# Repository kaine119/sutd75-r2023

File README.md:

# sutd-board-r2023
sutd kebord (manu + workshop early 2023)

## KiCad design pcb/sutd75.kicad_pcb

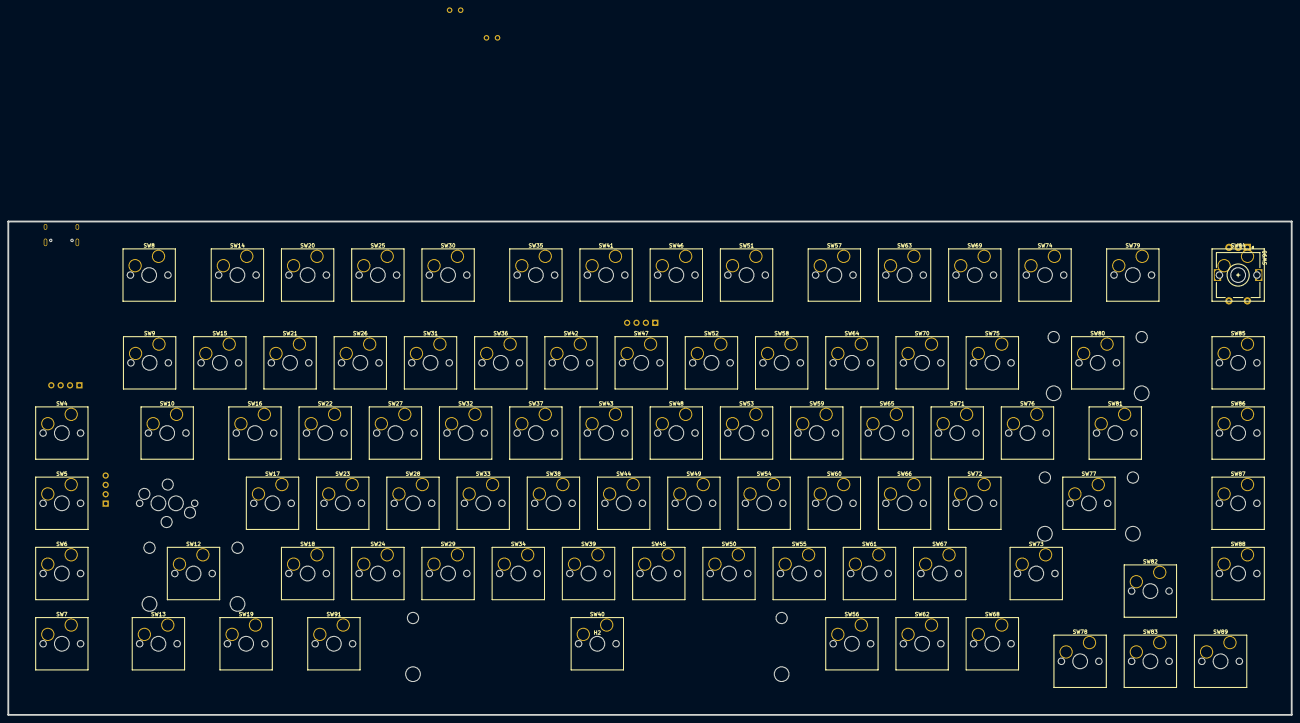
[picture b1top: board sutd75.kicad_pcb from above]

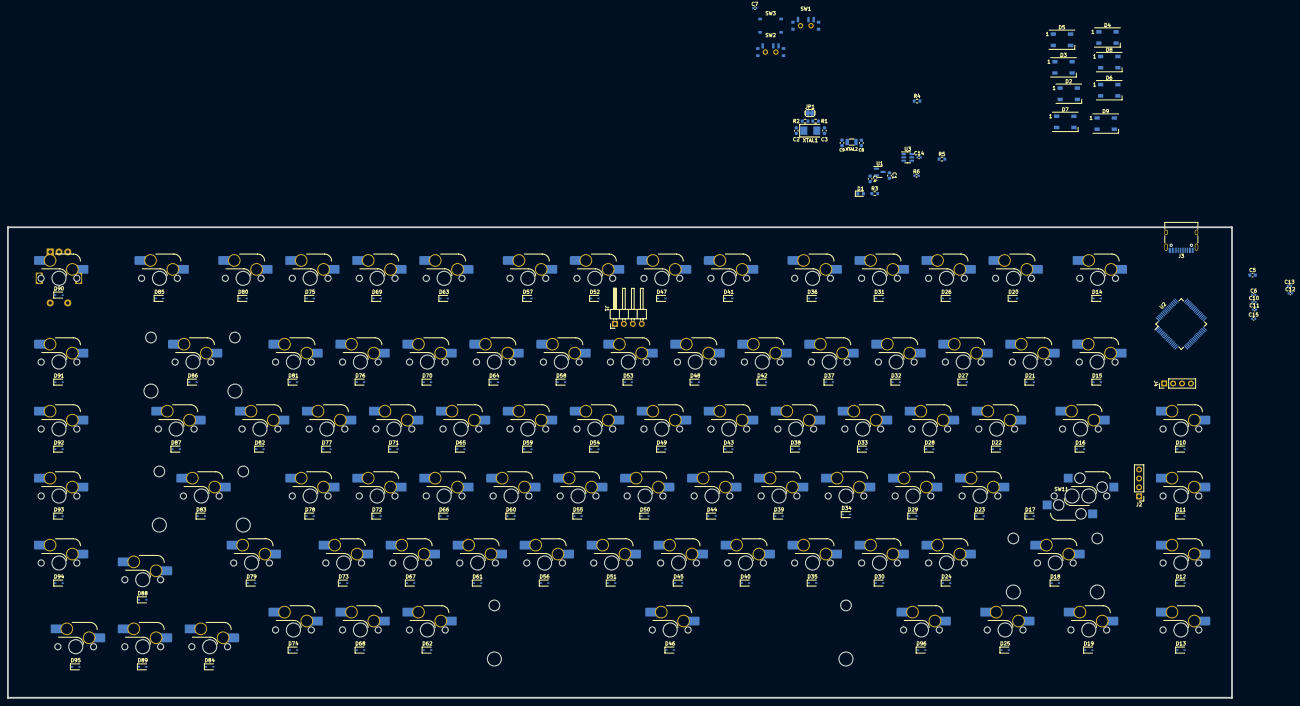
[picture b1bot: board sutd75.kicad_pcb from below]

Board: 2 copper layers, 348.1 x 133.8 mm, 222 parts (131 on the bottom side), 141 nets, no tracks yet.

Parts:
C1, C4: 1uF; C_0603_1608Metric
C2, C3: 30pF; C_0603_1608Metric
C5: 10uF; C_0603_1608Metric
C6, C7, C10, C11, C12, C13, C14, C15: 100nF; C_0402_1005Metric
C8, C9: 15pF; C_0603_1608Metric
D1: BLUE; LED_0603_1608Metric
D2, D3, D4, D5, D6, D7, D8, D9: WS2812B; LED_WS2812B_PLCC4_5.0x5.0mm_P3.2mm
D10, D11, D12, D13, D14, D15, D16, D17, D18, D19, D20, D21, D22, D23, D24, D25, D26, D27, D28, D29, D30, D31, D32, D33, D34, D35, D36, D37, D38, D39, D40, D41, D42, D43, D44, D45, D46, D47, D48, D49, D50, D51, D52, D53, D54, D55, D56, D57, D58, D59, D60, D61, D62, D63, D64, D65, D66, D67, D68, D69, D70, D71, D72, D73, D74, D75, D76, D77, D78, D79, D80, D81, D82, D83, D84, D85, D86, D87, D88, D89, D90, D91, D92, D93, D94, D95, D96: D; D_SOD-323
H1: LShift; Stabilizer_Cherry_MX_2u
H2: Space; Stabilizer_Cherry_MX_6.25u
H3: Enter; Stabilizer_Cherry_MX_2u
H4: Backspace; Stabilizer_Cherry_MX_2u
J1: SWD Header; PinHeader_1x04_P2.54mm_Horizontal
J2: UART header; PinHeader_1x04_P2.54mm_Vertical
J3: USB_C_Receptacle_USB2.0; USB_C_Receptacle_HRO_TYPE-C-31-M-12
J4: I2C header; PinHeader_1x04_P2.54mm_Vertical
JP1: SolderJumper_2_Open; SolderJumper-2_P1.3mm_Open_RoundedPad1.0x1.5mm
R1, R2: 200; R_0603_1608Metric
R3: 100; R_0603_1608Metric
R4, R5: 5.1k; R_0603_1608Metric
R6: 1.5k; R_0402_1005Metric_Pad0.72x0.64mm_HandSolder
SW1: BOOT0; SW_SPDTx01_SMD_AlpsAlpine-SSSS811101
SW2: BOOT1; SW_SPDTx01_SMD_AlpsAlpine-SSSS811101
SW3: RESET; SW_Push_SMD-SW-4_5.1x5.1x1.5
SW4: M1; SW_Hotswap_Kailh_MX_plated_1.00u
SW5: M2; SW_Hotswap_Kailh_MX_plated_1.00u
SW6: M3; SW_Hotswap_Kailh_MX_plated_1.00u
SW7: M4; SW_Hotswap_Kailh_MX_plated_1.00u
SW8: Esc; SW_Hotswap_Kailh_MX_plated_1.00u
SW9: Tilde; SW_Hotswap_Kailh_MX_plated_1.00u
SW10: Tab; SW_Hotswap_Kailh_MX_plated_1.50u
SW11: CapsLock; SW_Hotswap_Kailh_MX_1.75u_SteppedCapsLock
SW12: Shift; SW_Hotswap_Kailh_MX_plated_2.25u
SW13: Ctrl; SW_Hotswap_Kailh_MX_plated_1.25u
SW14: F1; SW_Hotswap_Kailh_MX_plated_1.00u
SW15: 1; SW_Hotswap_Kailh_MX_plated_1.00u
SW16: Q; SW_Hotswap_Kailh_MX_plated_1.00u
SW17: A; SW_Hotswap_Kailh_MX_plated_1.00u
SW18: Z; SW_Hotswap_Kailh_MX_plated_1.00u
SW19: Win; SW_Hotswap_Kailh_MX_plated_1.25u
SW20: F2; SW_Hotswap_Kailh_MX_plated_1.00u
SW21: 2; SW_Hotswap_Kailh_MX_plated_1.00u
SW22: W; SW_Hotswap_Kailh_MX_plated_1.00u
SW23: S; SW_Hotswap_Kailh_MX_plated_1.00u
SW24: X; SW_Hotswap_Kailh_MX_plated_1.00u
SW25: F3; SW_Hotswap_Kailh_MX_plated_1.00u
SW26: 3; SW_Hotswap_Kailh_MX_plated_1.00u
SW27: E; SW_Hotswap_Kailh_MX_plated_1.00u
SW28: D; SW_Hotswap_Kailh_MX_plated_1.00u
SW29: C; SW_Hotswap_Kailh_MX_plated_1.00u
SW30: F4; SW_Hotswap_Kailh_MX_plated_1.00u
SW31: 4; SW_Hotswap_Kailh_MX_plated_1.00u
SW32: R; SW_Hotswap_Kailh_MX_plated_1.00u
SW33: F; SW_Hotswap_Kailh_MX_plated_1.00u
SW34: V; SW_Hotswap_Kailh_MX_plated_1.00u
SW35: F5; SW_Hotswap_Kailh_MX_plated_1.00u
SW36: 5; SW_Hotswap_Kailh_MX_plated_1.00u
SW37: T; SW_Hotswap_Kailh_MX_plated_1.00u
SW38: G; SW_Hotswap_Kailh_MX_plated_1.00u
SW39: B; SW_Hotswap_Kailh_MX_plated_1.00u
SW40: Space; SW_Hotswap_Kailh_MX_plated_6.25u
SW41: F6; SW_Hotswap_Kailh_MX_plated_1.00u
SW42: 6; SW_Hotswap_Kailh_MX_plated_1.00u
SW43: Y; SW_Hotswap_Kailh_MX_plated_1.00u
SW44: H; SW_Hotswap_Kailh_MX_plated_1.00u
SW45: N; SW_Hotswap_Kailh_MX_plated_1.00u
SW46: F7; SW_Hotswap_Kailh_MX_plated_1.00u
SW47: 7; SW_Hotswap_Kailh_MX_plated_1.00u
SW48: U; SW_Hotswap_Kailh_MX_plated_1.00u
SW49: J; SW_Hotswap_Kailh_MX_plated_1.00u
SW50: M; SW_Hotswap_Kailh_MX_plated_1.00u
SW51: F8; SW_Hotswap_Kailh_MX_plated_1.00u
SW52: 8; SW_Hotswap_Kailh_MX_plated_1.00u
SW53: I; SW_Hotswap_Kailh_MX_plated_1.00u
SW54: K; SW_Hotswap_Kailh_MX_plated_1.00u
SW55: Comma; SW_Hotswap_Kailh_MX_plated_1.00u
SW56: RAlt; SW_Hotswap_Kailh_MX_plated_1.00u
SW57: F9; SW_Hotswap_Kailh_MX_plated_1.00u
SW58: 9; SW_Hotswap_Kailh_MX_plated_1.00u
SW59: O; SW_Hotswap_Kailh_MX_plated_1.00u
SW60: L; SW_Hotswap_Kailh_MX_plated_1.00u
SW61: Period; SW_Hotswap_Kailh_MX_plated_1.00u
SW62: RFn; SW_Hotswap_Kailh_MX_plated_1.00u
SW63: F10; SW_Hotswap_Kailh_MX_plated_1.00u
SW64: 0; SW_Hotswap_Kailh_MX_plated_1.00u
SW65: P; SW_Hotswap_Kailh_MX_plated_1.00u
SW66: Semicolon; SW_Hotswap_Kailh_MX_plated_1.00u
SW67: Slash; SW_Hotswap_Kailh_MX_plated_1.00u
SW68: RCtrl; SW_Hotswap_Kailh_MX_plated_1.00u
SW69: F11; SW_Hotswap_Kailh_MX_plated_1.00u
SW70: Minus; SW_Hotswap_Kailh_MX_plated_1.00u
SW71: LBrkt; SW_Hotswap_Kailh_MX_plated_1.00u
SW72: Quote; SW_Hotswap_Kailh_MX_plated_1.00u
SW73: RShift; SW_Hotswap_Kailh_MX_plated_1.75u
SW74: F12; SW_Hotswap_Kailh_MX_plated_1.00u
SW75: Equals; SW_Hotswap_Kailh_MX_plated_1.00u
SW76: RBrkt; SW_Hotswap_Kailh_MX_plated_1.00u
SW77: Enter; SW_Hotswap_Kailh_MX_plated_2.25u
SW78: LArr; SW_Hotswap_Kailh_MX_plated_1.00u
SW79: F13; SW_Hotswap_Kailh_MX_plated_1.00u
SW80: Bksp; SW_Hotswap_Kailh_MX_plated_2.00u
SW81: Bkslash; SW_Hotswap_Kailh_MX_plated_1.50u
SW82: UArr; SW_Hotswap_Kailh_MX_plated_1.00u
SW83: DArr; SW_Hotswap_Kailh_MX_plated_1.00u
SW84: Knob; SW_Hotswap_Kailh_MX_plated_1.00u
SW85: Home; SW_Hotswap_Kailh_MX_plated_1.00u
SW86: PgUp; SW_Hotswap_Kailh_MX_plated_1.00u
SW87: PgDn; SW_Hotswap_Kailh_MX_plated_1.00u
SW88: End; SW_Hotswap_Kailh_MX_plated_1.00u
SW89: RArr; SW_Hotswap_Kailh_MX_plated_1.00u
SW90: Rotary_Encoder_Switch; RotaryEncoder_Alps_EC11E-Switch_Vertical_H20mm
SW91: Alt; SW_Hotswap_Kailh_MX_plated_1.25u
U1: XC6206PxxxMR; SOT-23
U2: STM32F103RBTx; LQFP-64_10x10mm_P0.5mm
U3: USBLC6-2SC6; SOT-23-6
XTAL1: 8MHz; Crystal_SMD_5032-2Pin_5.0x3.2mm
XTAL2: 32.768kHz; Crystal_SMD_3215-2Pin_3.2x1.5mm

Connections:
+3V3: C4.1, C5.1, C6.1, C10.1, C11.1, C12.1, C13.2, C15.1, D1.2 (A), J1.4, J4.2, R6.1, SW1.1 (A), SW2.1 (A), U1.2 (VO), U2.1 (VBAT), U2.13 (VDDA), U2.19 (VDD), U2.32 (VDD), U2.48 (VDD), U2.64 (VDD)
/BOOT0: SW1.2 (B), U2.60 (BOOT0)
/BOOT1: SW2.2 (B), U2.28 (PB2)
/COL1: SW4.1, SW5.1, SW6.1, SW7.1, U2.35 (PB14)
/COL2: SW8.1, SW9.1, SW10.1, SW11.1, SW12.1, SW13.1, U2.34 (PB13)
/COL3: SW14.1, SW15.1, SW16.1, SW17.1, SW18.1, SW19.1, U2.33 (PB12)
/COL4: SW20.1, SW21.1, SW22.1, SW23.1, SW24.1, SW91.1, U2.30 (PB11)
/COL5: SW25.1, SW26.1, SW27.1, SW28.1, SW29.1, U2.29 (PB10)
/COL6: SW30.1, SW31.1, SW32.1, SW33.1, SW34.1, U2.27 (PB1)
/COL7: SW35.1, SW36.1, SW37.1, SW38.1, SW39.1, SW40.1, U2.26 (PB0)
/COL8: SW41.1, SW42.1, SW43.1, SW44.1, SW45.1, U2.36 (PB15)
/COL9: SW46.1, SW47.1, SW48.1, SW49.1, SW50.1, U2.62 (PB9)
/COL10: SW51.1, SW52.1, SW53.1, SW54.1, SW55.1, SW56.1, U2.61 (PB8)
/COL11: SW57.1, SW58.1, SW59.1, SW60.1, SW61.1, SW62.1, U2.59 (PB7)
/COL12: SW63.1, SW64.1, SW65.1, SW66.1, SW67.1, SW68.1, U2.58 (PB6)
/COL13: SW69.1, SW70.1, SW71.1, SW72.1, SW73.1, U2.57 (PB5)
/COL14: SW74.1, SW75.1, SW76.1, SW77.1, SW78.1, U2.56 (PB4)
/COL15: SW79.1, SW80.1, SW81.1, SW82.1, SW83.1, U2.55 (PB3)
/COL16: SW84.1, SW85.1, SW86.1, SW87.1, SW88.1, SW89.1, SW90.S1, U2.50 (PA15)
/HSE_IN: C2.1, U2.5 (PD0), XTAL1.1
/HSE_OUT: JP1.2 (B), R2.2, U2.6 (PD1)
/KNOB_A: SW90.A, U2.23 (PA7)
/KNOB_B: SW90.B, U2.22 (PA6)
/LSE_IN: C8.1, U2.3 (PC14), XTAL2.1
/LSE_OUT: C9.2, U2.4 (PC15), XTAL2.2
/NRST: C7.2, SW3.1, U2.7 (NRST)
/ROW1: D14.2 (A), D20.2 (A), D26.2 (A), D31.2 (A), D36.2 (A), D41.2 (A), D47.2 (A), D52.2 (A), D57.2 (A), D63.2 (A), D69.2 (A), D75.2 (A), D80.2 (A), D85.2 (A), D90.2 (A), U2.14 (PA0)
/ROW2: D15.2 (A), D21.2 (A), D27.2 (A), D32.2 (A), D37.2 (A), D42.2 (A), D48.2 (A), D53.2 (A), D58.2 (A), D64.2 (A), D70.2 (A), D76.2 (A), D81.2 (A), D86.2 (A), D91.2 (A), U2.15 (PA1)
/ROW3: D10.2 (A), D16.2 (A), D22.2 (A), D28.2 (A), D33.2 (A), D38.2 (A), D43.2 (A), D49.2 (A), D54.2 (A), D59.2 (A), D65.2 (A), D71.2 (A), D77.2 (A), D82.2 (A), D87.2 (A), D92.2 (A), U2.16 (PA2)
/ROW4: D11.2 (A), D17.2 (A), D23.2 (A), D29.2 (A), D34.2 (A), D39.2 (A), D44.2 (A), D50.2 (A), D55.2 (A), D60.2 (A), D66.2 (A), D72.2 (A), D78.2 (A), D83.2 (A), D93.2 (A), U2.17 (PA3)
/ROW5: D12.2 (A), D18.2 (A), D24.2 (A), D30.2 (A), D35.2 (A), D40.2 (A), D45.2 (A), D51.2 (A), D56.2 (A), D61.2 (A), D67.2 (A), D73.2 (A), D79.2 (A), D88.2 (A), D94.2 (A), U2.20 (PA4)
/ROW6: D13.2 (A), D19.2 (A), D25.2 (A), D46.2 (A), D62.2 (A), D68.2 (A), D74.2 (A), D84.2 (A), D89.2 (A), D95.2 (A), D96.2 (A), U2.21 (PA5)
/SWCLK: J1.2, U2.49 (PA14)
/SWDIO: J1.3, U2.46 (PA13)
/UART1_RX: J2.2, U2.43 (PA10)
/UART1_TX: J2.3, U2.42 (PA9)
/USB_CC1: J3.B5 (CC2), R5.1
/USB_CC2: J3.A5 (CC1), R4.1
/USB_D+: R6.2, U2.45 (PA12), U3.4 (I/O2)
/USB_D-: U2.44 (PA11), U3.6 (I/O1)
GND: C1.2, C2.2, C3.2, C4.2, C5.2, C6.2, C7.1, C8.2, C9.1, C10.2, C11.2, C12.2, C13.1, C14.2, C15.2, D2.1 (VDD), D3.1 (VDD), D4.1 (VDD), D5.1 (VDD), D6.3 (VSS), D7.3 (VSS), D8.3 (VSS), D9.3 (VSS), J1.1, J2.4, J3.A1 (GND), J3.A12 (GND), J3.B1 (GND), J3.B12 (GND), J3.S1 (SHIELD), J4.1, R3.1, R4.2, R5.2, SW1.3 (C), SW2.3 (C), SW3.2, SW90.C, U1.1 (GND), U2.12 (VSSA), U2.18 (VSS), U2.31 (VSS), U2.47 (VSS), U2.63 (VSS), U3.2 (GND)
unnamed: C3.1, JP1.1 (A), R1.1, XTAL1.2
unnamed: D1.1 (K), R3.2
unnamed: D2.2 (DOUT), D3.4 (DIN)
unnamed: D3.2 (DOUT), D4.4 (DIN)
unnamed: D4.2 (DOUT), D5.4 (DIN)
unnamed: D5.2 (DOUT), D9.4 (DIN)
unnamed: D6.4 (DIN), D7.2 (DOUT)
unnamed: D7.4 (DIN), D8.2 (DOUT)
unnamed: D8.4 (DIN), D9.2 (DOUT)
unnamed: D10.1 (K), SW4.2
unnamed: D11.1 (K), SW5.2
unnamed: D12.1 (K), SW6.2
unnamed: D13.1 (K), SW7.2
unnamed: D14.1 (K), SW8.2
unnamed: D15.1 (K), SW9.2
unnamed: D16.1 (K), SW10.2
unnamed: D17.1 (K), SW11.2
unnamed: D18.1 (K), SW12.2
unnamed: D19.1 (K), SW13.2
unnamed: D20.1 (K), SW14.2
unnamed: D21.1 (K), SW15.2
unnamed: D22.1 (K), SW16.2
unnamed: D23.1 (K), SW17.2
unnamed: D24.1 (K), SW18.2
unnamed: D25.1 (K), SW19.2
unnamed: D26.1 (K), SW20.2
unnamed: D27.1 (K), SW21.2
unnamed: D28.1 (K), SW22.2
unnamed: D29.1 (K), SW23.2
unnamed: D30.1 (K), SW24.2
unnamed: D31.1 (K), SW25.2
unnamed: D32.1 (K), SW26.2
unnamed: D33.1 (K), SW27.2
unnamed: D34.1 (K), SW28.2
unnamed: D35.1 (K), SW29.2
unnamed: D36.1 (K), SW30.2
unnamed: D37.1 (K), SW31.2
unnamed: D38.1 (K), SW32.2
unnamed: D39.1 (K), SW33.2
unnamed: D40.1 (K), SW34.2
unnamed: D41.1 (K), SW35.2
unnamed: D42.1 (K), SW36.2
unnamed: D43.1 (K), SW37.2
unnamed: D44.1 (K), SW38.2
unnamed: D45.1 (K), SW39.2
unnamed: D46.1 (K), SW40.2
unnamed: D47.1 (K), SW41.2
unnamed: D48.1 (K), SW42.2
unnamed: D49.1 (K), SW43.2
unnamed: D50.1 (K), SW44.2
unnamed: D51.1 (K), SW45.2
unnamed: D52.1 (K), SW46.2
unnamed: D53.1 (K), SW47.2
unnamed: D54.1 (K), SW48.2
unnamed: D55.1 (K), SW49.2
unnamed: D56.1 (K), SW50.2
unnamed: D57.1 (K), SW51.2
unnamed: D58.1 (K), SW52.2
unnamed: D59.1 (K), SW53.2
unnamed: D60.1 (K), SW54.2
unnamed: D61.1 (K), SW55.2
unnamed: D62.1 (K), SW56.2
unnamed: D63.1 (K), SW57.2
unnamed: D64.1 (K), SW58.2
unnamed: D65.1 (K), SW59.2
unnamed: D66.1 (K), SW60.2
unnamed: D67.1 (K), SW61.2
unnamed: D68.1 (K), SW62.2
unnamed: D69.1 (K), SW63.2
unnamed: D70.1 (K), SW64.2
unnamed: D71.1 (K), SW65.2
unnamed: D72.1 (K), SW66.2
unnamed: D73.1 (K), SW67.2
unnamed: D74.1 (K), SW68.2
unnamed: D75.1 (K), SW69.2
unnamed: D76.1 (K), SW70.2
unnamed: D77.1 (K), SW71.2
unnamed: D78.1 (K), SW72.2
unnamed: D79.1 (K), SW73.2
unnamed: D80.1 (K), SW74.2
unnamed: D82.1 (K), SW76.2
unnamed: D83.1 (K), SW77.2
unnamed: D84.1 (K), SW78.2
unnamed: D85.1 (K), SW79.2
unnamed: D86.1 (K), SW80.2
unnamed: D87.1 (K), SW81.2
unnamed: D88.1 (K), SW82.2
unnamed: D89.1 (K), SW83.2
unnamed: D90.1 (K), SW84.2, SW90.S2
unnamed: D91.1 (K), SW85.2
unnamed: D92.1 (K), SW86.2
unnamed: D93.1 (K), SW87.2
unnamed: D94.1 (K), SW88.2
unnamed: D95.1 (K), SW89.2
unnamed: D96.1 (K), SW91.2
unnamed: J3.A6 (D+), J3.B6 (D+), U3.3 (I/O2)
unnamed: J3.A7 (D-), J3.B7 (D-), U3.1 (I/O1)
unnamed: R1.2, R2.1
unnamed: D81.1 (K), SW75.2
VBUS: C1.1, C14.1, D2.3 (VSS), D3.3 (VSS), D4.3 (VSS), D5.3 (VSS), D6.1 (VDD), D7.1 (VDD), D8.1 (VDD), D9.1 (VDD), J2.1, J3.A4 (VBUS), J3.A9 (VBUS), J3.B4 (VBUS), J3.B9 (VBUS), U1.3 (VI), U3.5 (VBUS)

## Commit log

2022-11-24 Add preliminary ideas for keyboard layout
2022-11-24 Add PCB files
    STM32 implementation came from Arism75.
2022-11-25 Move knob footprint in layout file a bit to the right
2022-11-25 Add keyboard layout to pcb layout
2022-11-27 Use stepped caps lock footprint from my fork of keyswitch-kicad-library
2022-11-27 Arrange the rest of the switches
2022-11-27 Group some of the components together first
2022-11-27 Wire up power circuitry
2022-11-27 Add plate files
2022-11-27 Change value fields for socket assembly
2022-11-28 Add routing for rows and some of the columns
2022-12-05 Wire up switch sockets to diodes
2022-12-05 Move SWD header, fix DRC issues
2022-12-05 Add 3d models for switches to all footprints
2022-12-05 Move silkscreen around
2022-12-05 Shift the underglow LEDs around a bit
2022-12-05 Add solder bridge for power led, add silkscreen for pin headers
2022-12-28 [layout] Change right mods to 1.25u
2022-12-28 Fix DRC
2022-12-29 [admin] Force git to commit with LF
2022-12-29 Update PCB with new layout for right mods
2022-12-29 Round PCB corners
2022-12-29 Add dimensions
2022-12-29 Replace AlpsAlpine-SSSS811101 with AlpsAlpine-SSSS710607 for boot toggle
2022-12-29 Update schematic and BOM with new AlpsAlpine part
2022-12-30 Update DXFs for switch and keycap layers
2022-12-30 Actually draw out a plate
2023-01-16 Add breakout pin header for unused pins on MCU
2023-01-16 Realign original plate layout
2023-01-16 Bump down clearance on plate stabilizer holes
2023-01-16 Actually trace the correct line for the plate
2023-01-16 Fix a ground plane
2023-01-16 Align top and bottom edges with edges of keycaps
2023-01-25 Fix plate gasket mount dimensions
2023-01-25 Reduce gap between plate feet and plate to 2mm
2023-01-30 Cleanup tracks & vias
2023-01-30 Cleanup a track
2023-02-03 Shorten plate correspondingly
2023-06-16 cleanup for quote
2023-06-29 Update files for KiCad 7
2023-06-29 Add plate backups to gitignore
2023-06-29 Add optional pullup resistors to I2C screen footprint, update footprints
2023-06-29 Touch up silkscreen
2023-06-29 deal with DRC
2023-06-30 Extend USB port
2023-06-30 Touch up silkscreen and schematic
2023-08-01 Fix SWD silkscreen and boot toggles
2023-08-01 Move RGBLED_DIN line to a PWM pin, fix rotary encoder pad overlap
2023-09-24 Make caps lock footprint two separate symbols and footprints
    ...so that JLCPCB will actually solder them both
2023-09-24 Cut out wider hole for stepped caps lock on plate
